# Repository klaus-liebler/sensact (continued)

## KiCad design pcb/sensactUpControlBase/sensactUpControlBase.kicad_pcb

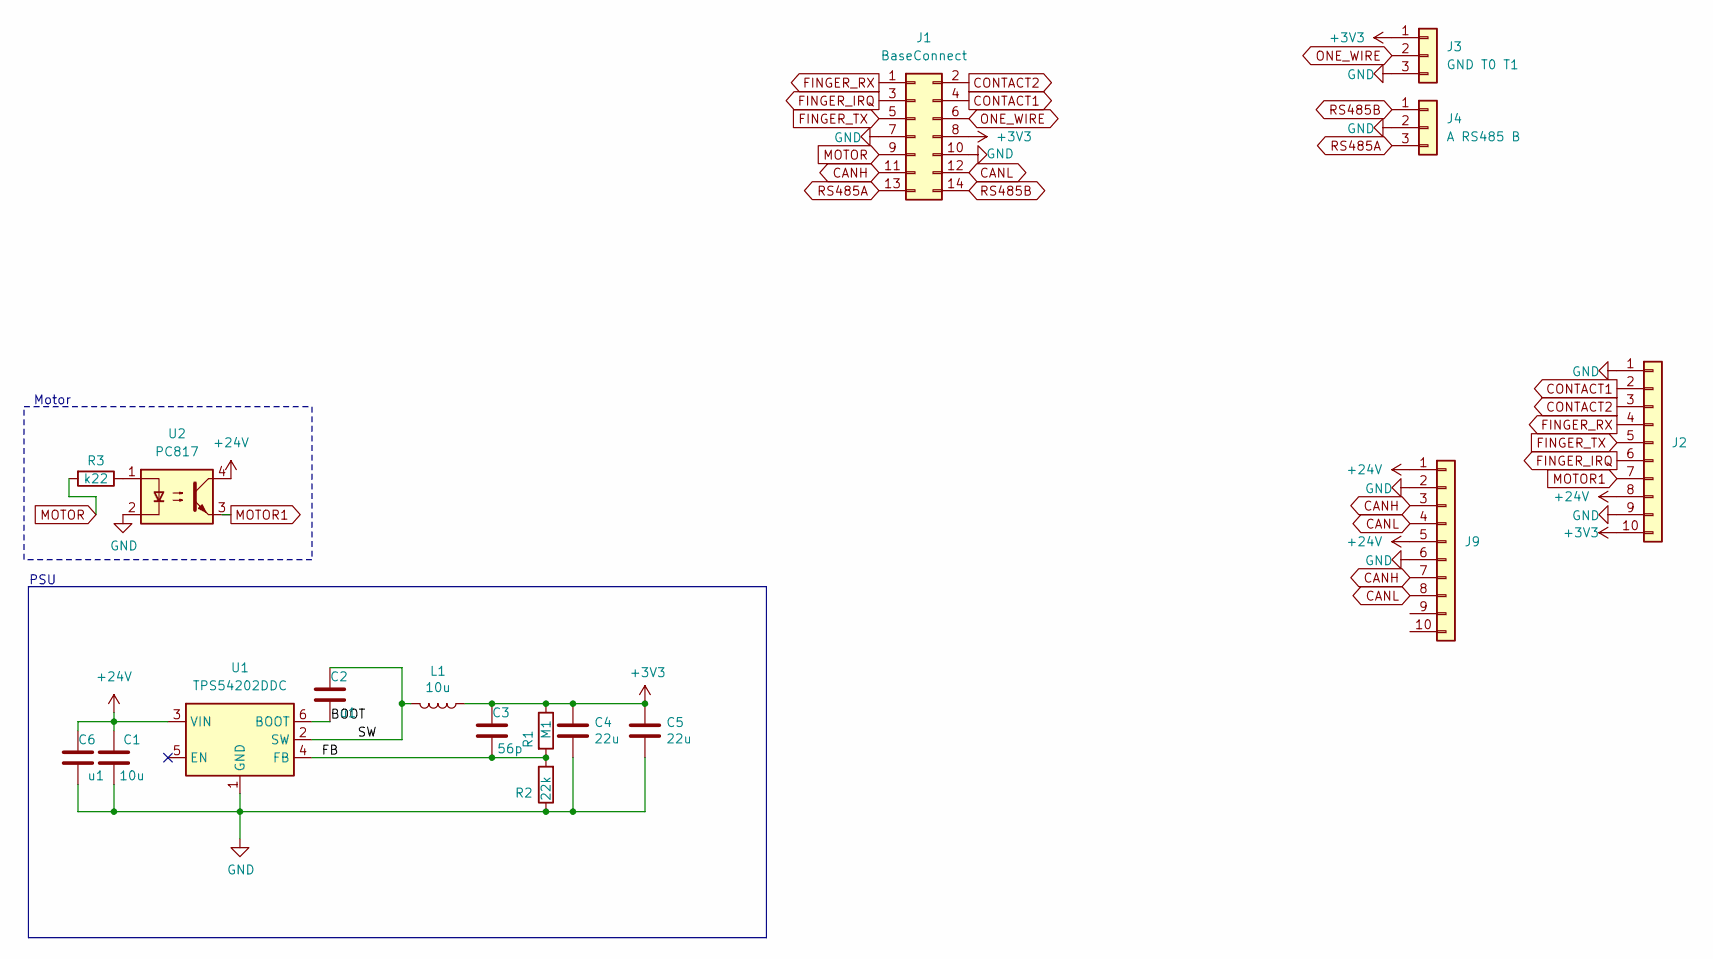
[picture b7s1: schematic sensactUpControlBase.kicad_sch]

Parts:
C1: 10u; C_1206_3216Metric_Pad1.33x1.80mm_HandSolder
C2, C6: u1; C_0805_2012Metric_Pad1.18x1.45mm_HandSolder
C3: 56p; C_0805_2012Metric_Pad1.18x1.45mm_HandSolder
C4, C5: 22u; C_0805_2012Metric_Pad1.18x1.45mm_HandSolder
J1: BaseConnect; PinHeader_2x07_P2.54mm_Vertical
J2, J9: WAGO_250-210
J3: GND T0 T1; WAGO_250_203A
J4: A RS485 B; WAGO_250_203A
L1: 10u; L_0630
R1: M1; R_0805_2012Metric_Pad1.20x1.40mm_HandSolder
R2: 22k; R_0805_2012Metric_Pad1.20x1.40mm_HandSolder
R3: k22; R_0805_2012Metric_Pad1.20x1.40mm_HandSolder
U1: TPS54202DDC; SOT-23-6_Handsoldering
U2: PC817; mdip_4_handsolder

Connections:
+3V3: C3.2, C4.1, C5.1, J1.8, J2.10, J3.1, L1.1, R1.1
+24V: C1.2, C6.2, J2.8, J9.1, J9.5, U1.3 (VIN), U2.4
/BOOT: C2.1, U1.6 (BOOT)
/FB: C3.1, R1.2, R2.2, U1.4 (FB)
/SW: C2.2, L1.2, U1.2 (SW)
CANH: J1.11, J9.3, J9.7
CANL: J1.12, J9.4, J9.8
CONTACT1: J1.4, J2.2
CONTACT2: J1.2, J2.3
FINGER_IRQ: J1.3, J2.6
FINGER_RX: J1.1, J2.4
FINGER_TX: J1.5, J2.5
GND: C1.1, C4.2, C5.2, C6.1, J1.7, J1.10, J2.1, J2.9, J3.3, J4.2, J9.2, J9.6, R2.1, U1.1 (GND), U2.2
MOTOR: J1.9, R3.2
MOTOR1: J2.7, U2.3
unnamed: R3.1, U2.1
ONE_WIRE: J1.6, J3.2
RS485A: J1.13, J4.3
RS485B: J1.14, J4.1

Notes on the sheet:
Motor
PSU

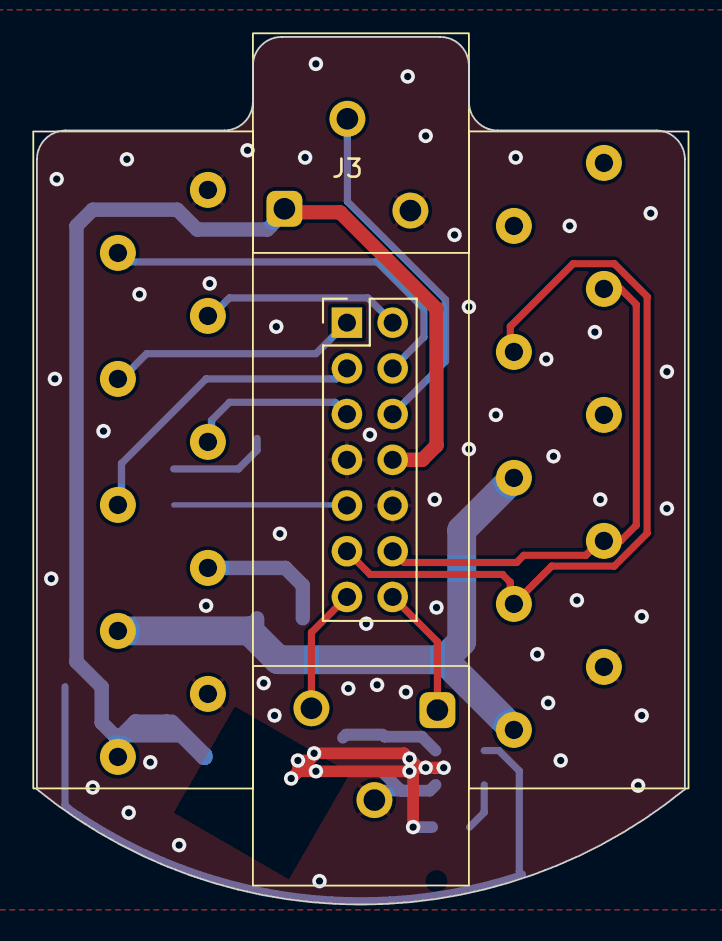
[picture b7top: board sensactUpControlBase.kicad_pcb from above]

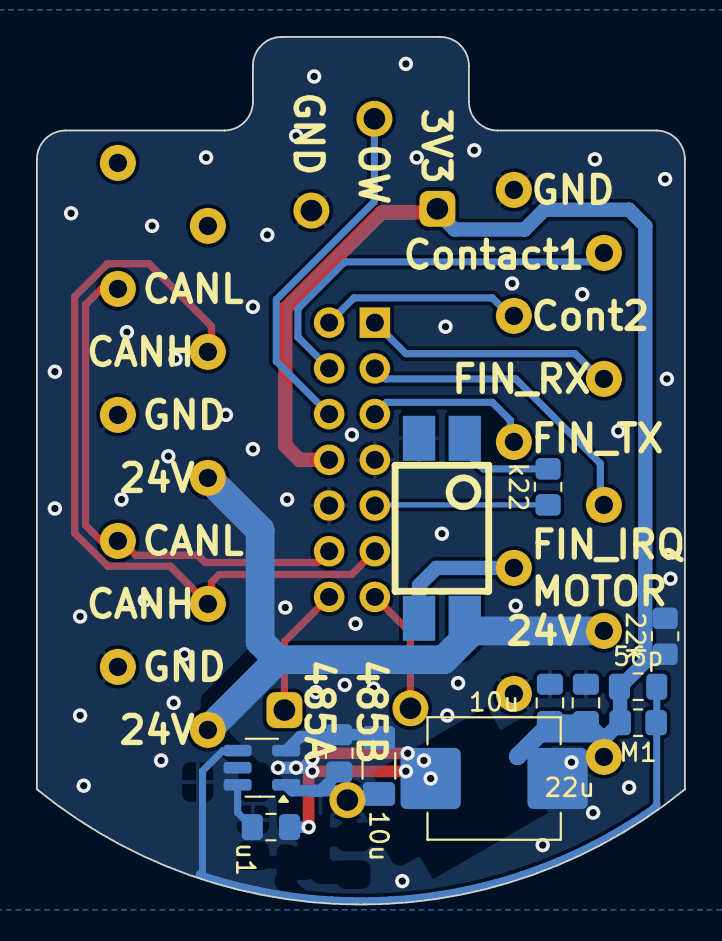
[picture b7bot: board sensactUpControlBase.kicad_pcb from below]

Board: 2 copper layers, 36.0 x 48.2 mm, 17 parts (12 on the bottom side), 19 nets.

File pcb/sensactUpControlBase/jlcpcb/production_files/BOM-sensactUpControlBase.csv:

Comment,Designator,Footprint,LCSC
10u,L1,L_0630,
GND T0 T1,J3,KF250-3.5-3P-A,
BaseConnect,J1,PinHeader_2x07_P2.54mm_Vertical,
~,J9,WAGO_250-210,
A RS485 B,J4,KF250-3.5-3P-A,
~,J2,WAGO_250-210,
22u,C4,C_0805_2012Metric_Pad1.18x1.45mm_HandSolder,
10u,C1,C_1206_3216Metric_Pad1.33x1.80mm_HandSolder,
56p,C3,C_0805_2012Metric_Pad1.18x1.45mm_HandSolder,
u1,C2,C_0805_2012Metric_Pad1.18x1.45mm_HandSolder,
PC817,U2,mdip_4_handsolder,
22u,C5,C_0805_2012Metric_Pad1.18x1.45mm_HandSolder,
22k,R2,R_0805_2012Metric_Pad1.20x1.40mm_HandSolder,
M1,R1,R_0805_2012Metric_Pad1.20x1.40mm_HandSolder,
k22,R3,R_0805_2012Metric_Pad1.20x1.40mm_HandSolder,
TPS54202DDC,U1,SOT-23-6_Handsoldering,

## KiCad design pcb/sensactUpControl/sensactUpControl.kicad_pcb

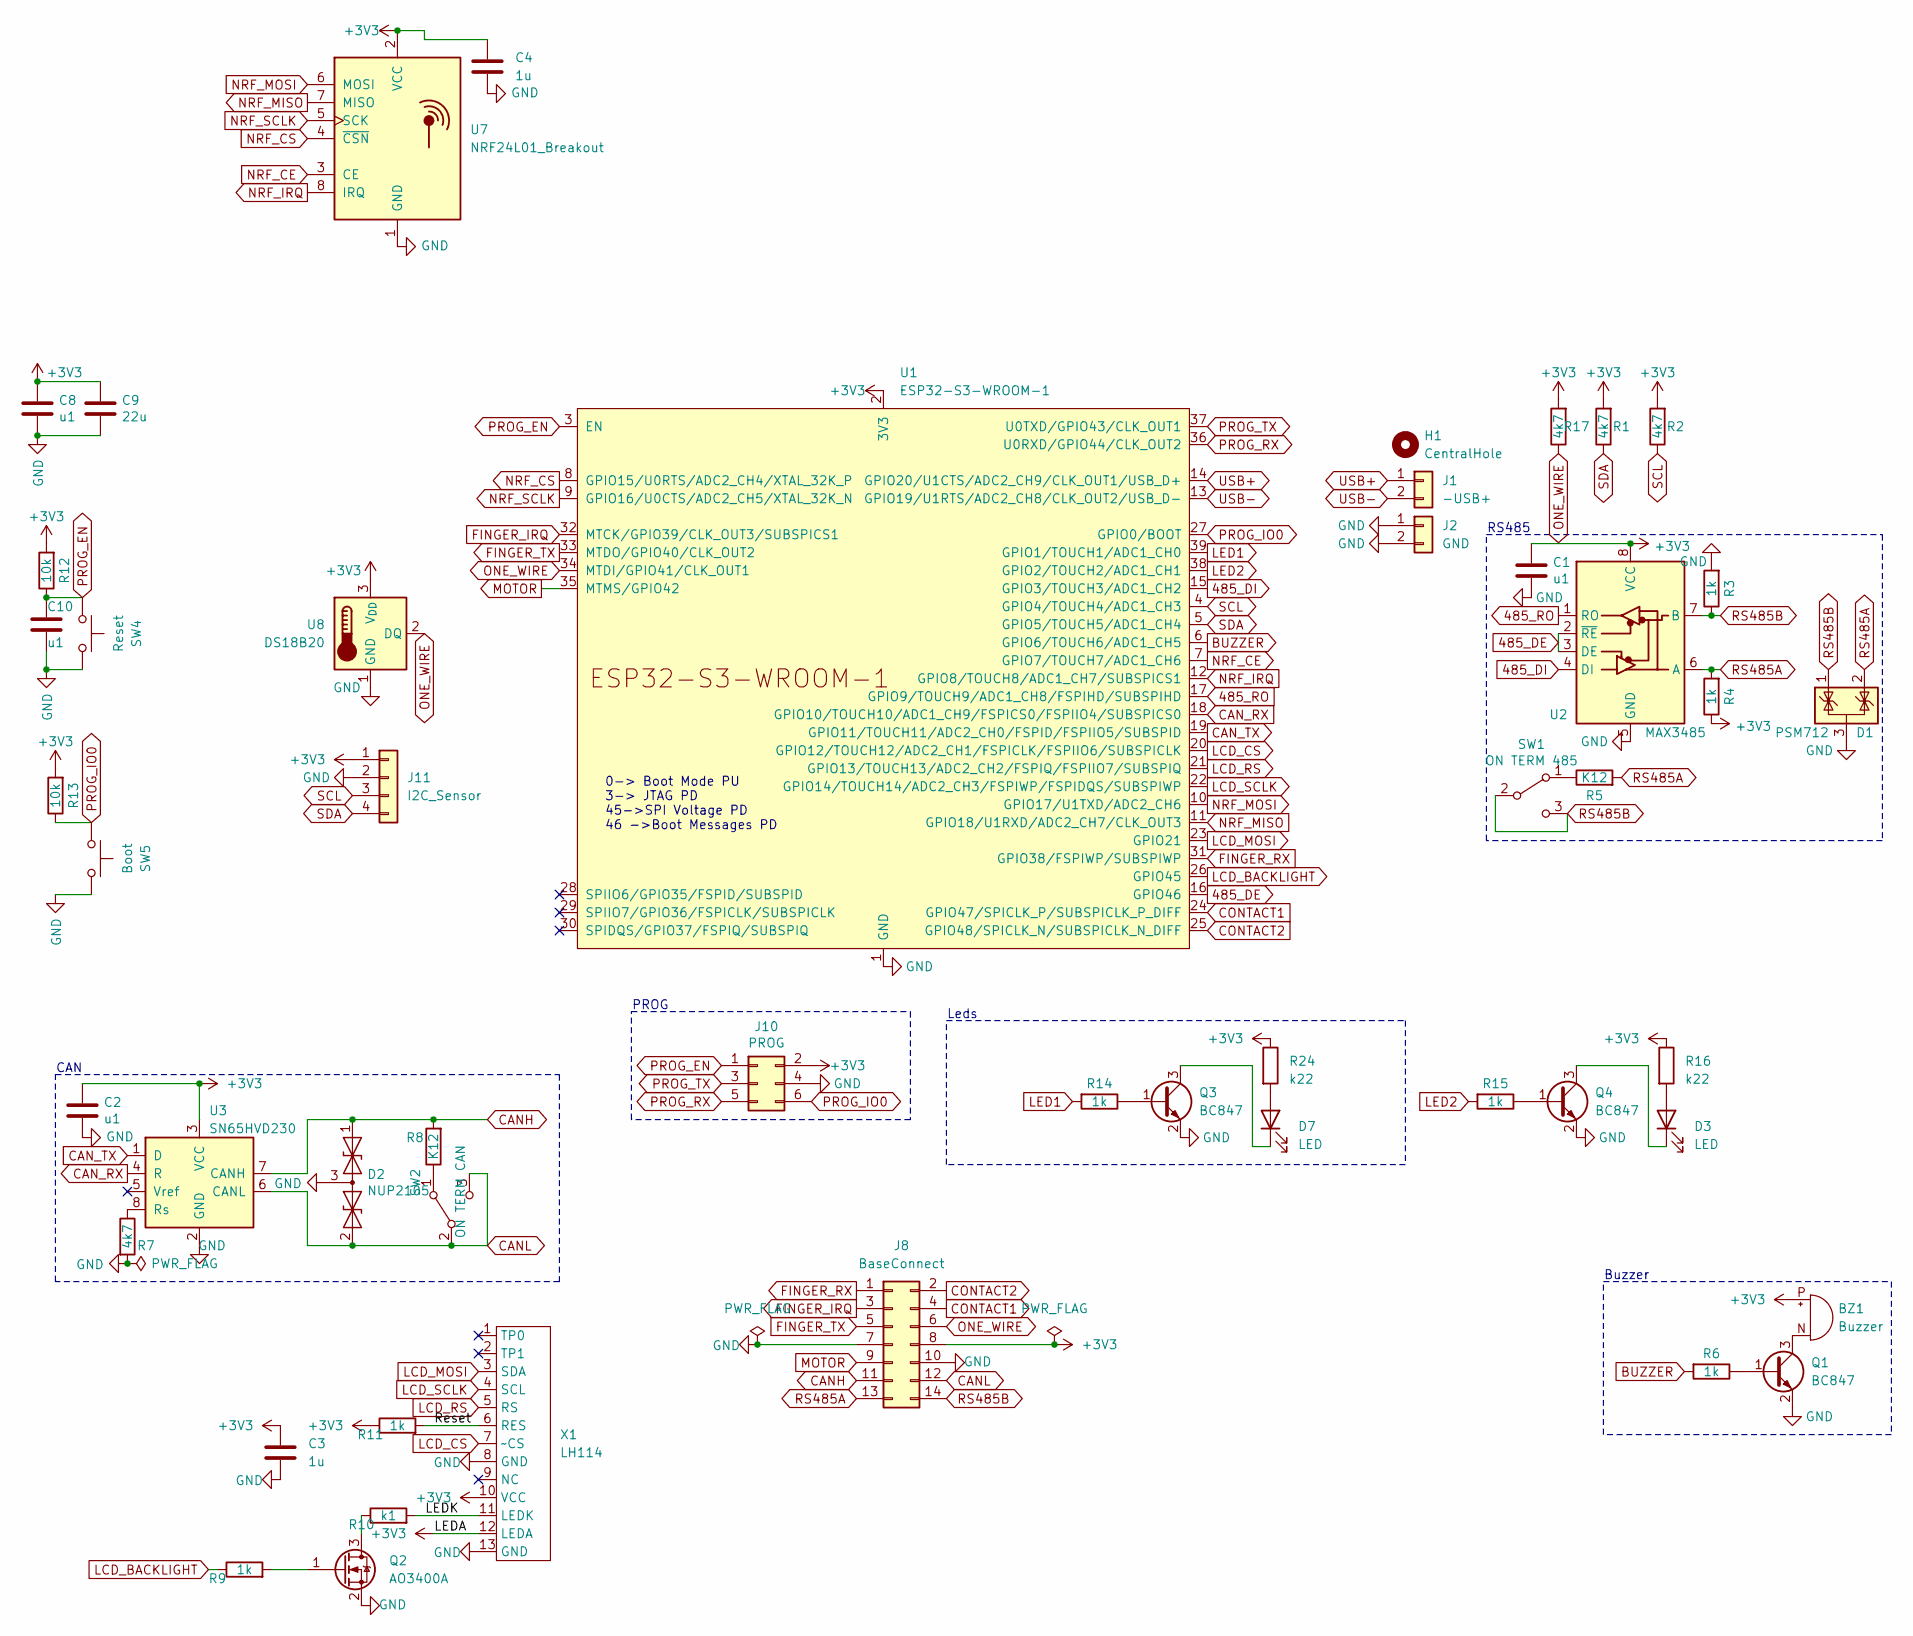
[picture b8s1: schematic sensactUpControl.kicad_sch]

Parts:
BZ1: Buzzer; XDCR_CMT-7525-80-SMT-TR_handsolder
C1, C2, C8, C10: u1; C_0805_2012Metric_Pad1.18x1.45mm_HandSolder
C3, C4: 1u; C_0805_2012Metric_Pad1.18x1.45mm_HandSolder
C9: 22u; C_0805_2012Metric_Pad1.18x1.45mm_HandSolder
D1: PSM712; SOT-23_Handsoldering
D2: NUP2105; SOT-23_Handsoldering
D3, D7: LED; LED_PLCC_2835_Handsoldering
H1: CentralHole; MountingHole_3.2mm_M3
J1: -USB+; PinHeader_1x02_P2.00mm_Vertical
J2: GND; PinHeader_1x02_P2.00mm_Vertical
J8: BaseConnect; PinHeader_2x07_P2.54mm_Vertical
J10: PROG; IDC_2x03_P1.27mm_Vertical
J11: I2C_Sensor; PinHeader_1x04_P2.54mm_Vertical
Q1, Q3, Q4: BC847; SOT-23_Handsoldering
Q2: AO3400A; SOT-23_Handsoldering
R1, R2, R7, R17: 4k7; R_0805_2012Metric_Pad1.20x1.40mm_HandSolder
R3, R4, R6, R9, R11, R14, R15: 1k; R_0805_2012Metric_Pad1.20x1.40mm_HandSolder
R5, R8: K12; R_1206_3216Metric_Pad1.30x1.75mm_HandSolder
R10: k1; R_0805_2012Metric_Pad1.20x1.40mm_HandSolder
R12, R13: 10k; R_0805_2012Metric_Pad1.20x1.40mm_HandSolder
R16, R24: k22; R_1206_3216Metric_Pad1.30x1.75mm_HandSolder
SW1: ON TERM 485; SW_SPDT_PCM12_handsolder
SW2: ON TERM CAN; SW_SPDT_PCM12_handsolder
SW4: Reset; SW_SPST_TL3342_smaller_handsolder
SW5: Boot; SW_SPST_TL3342_smaller_handsolder
U1: ESP32-S3-WROOM-1; ESP32-S3-WROOM-1_handsolder
U2: MAX3485; SOIC-8_3.9x4.9mm_Pitch1.27mm_handsolder
U3: SN65HVD230; SOIC-8_3.9x4.9mm_Pitch1.27mm_handsolder
U7: NRF24L01_Breakout; nRF24L01_Breakout
U8: DS18B20; TO-92_HandSolder
X1: LH114; FP-114 13pol top only

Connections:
485_DE: U1.16 (GPIO46), U2.2 (~RE), U2.3 (DE)
485_DI: U1.15 (GPIO3/TOUCH3/ADC1_CH2), U2.4 (DI)
485_RO: U1.17 (GPIO9/TOUCH9/ADC1_CH8/FSPIHD/SUBSPIHD), U2.1 (RO)
+3V3: BZ1.P (+), C1.2, C2.1, C3.1, C4.1, C8.1, C9.1, J8.8, J10.2, J11.1, R1.2, R2.2, R4.1, R11.1, R12.2, R13.2, R16.1, R17.2, R24.1, U1.2 (3V3), U2.8 (VCC), U3.3 (VCC), U7.2 (VCC), U8.3 (V_{DD}), X1.10 (VCC), X1.12 (LEDA)
/LEDK: R10.2, X1.11 (LEDK)
/Reset: R11.2, X1.6 (RES)
BUZZER: R6.2, U1.6 (GPIO6/TOUCH6/ADC1_CH5)
CANH: D2.1 (A1), J8.11, R8.2, U3.7 (CANH)
CANL: D2.2 (A2), J8.12, SW2.2 (B), SW2.3 (C), U3.6 (CANL)
CAN_RX: U1.18 (GPIO10/TOUCH10/ADC1_CH9/FSPICS0/FSPIIO4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), U3.4 (R)
CAN_TX: U1.19 (GPIO11/TOUCH11/ADC2_CH0/FSPID/FSPIIO5/S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), U3.1 (D)
CONTACT1: J8.4, U1.24 (GPIO47/SPICLK_P/SUBSPICLK_P_DIFF)
CONTACT2: J8.2, U1.25 (GPIO48/SPICLK_N/SUBSPICLK_N_DIFF)
FINGER_IRQ: J8.3, U1.32 (MTCK/GPIO39/CLK_OUT3/SUBSPICS1)
FINGER_RX: J8.1, U1.31 (GPIO38/FSPIWP/SUBSPIWP)
FINGER_TX: J8.5, U1.33 (MTDO/GPIO40/CLK_OUT2)
GND: C1.1, C2.2, C3.2, C4.2, C8.2, C9.2, C10.2, D1.3 (A), D2.3 (common), J2.1, J2.2, J8.7, J8.10, J10.4, J11.2, Q1.2 (E), Q2.2 (S), Q3.2 (E), Q4.2 (E), R3.2, R7.2, SW4.1, SW5.1, U1.1 (GND), U1.40 (GND), U1.41 (GND), U2.5 (GND), U3.2 (GND), U7.1 (GND), U8.1 (GND), X1.8 (GND), X1.13 (GND)
LCD_BACKLIGHT: R9.1, U1.26 (GPIO45)
LCD_CS: U1.20 (GPIO12/TOUCH12/ADC2_CH1/FSPICLK/FSPIIO6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), X1.7 (~CS)
LCD_MOSI: U1.23 (GPIO21), X1.3 (SDA)
LCD_RS: U1.21 (GPIO13/TOUCH13/ADC2_CH2/FSPIQ/FSPIIO7/S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), X1.5 (RS)
LCD_SCLK: U1.22 (GPIO14/TOUCH14/ADC2_CH3/FSPIWP/FSPIDQS/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), X1.4 (SCL)
LED1: R14.2, U1.39 (GPIO1/TOUCH1/ADC1_CH0)
LED2: R15.2, U1.38 (GPIO2/TOUCH2/ADC1_CH1)
MOTOR: J8.9, U1.35 (MTMS/GPIO42)
NRF_CE: U1.7 (GPIO7/TOUCH7/ADC1_CH6), U7.3 (CE)
NRF_CS: U1.8 (GPIO15/U0RTS/ADC2_CH4/XTAL_32K_P), U7.4 (~CSN)
NRF_IRQ: U1.12 (GPIO8/TOUCH8/ADC1_CH7/SUBSPICS1), U7.8 (IRQ)
NRF_MISO: U1.11 (GPIO18/U1RXD/ADC2_CH7/CLK_OUT3), U7.7 (MISO)
NRF_MOSI: U1.10 (GPIO17/U1TXD/ADC2_CH6), U7.6 (MOSI)
NRF_SCLK: U1.9 (GPIO16/U0CTS/ADC2_CH5/XTAL_32K_N), U7.5 (SCK)
unnamed: BZ1.N (-), Q1.3 (C)
unnamed: D3.2 (A), R16.2
unnamed: D3.1 (K), Q4.3 (C)
unnamed: D7.2 (A), R24.2
unnamed: D7.1 (K), Q3.3 (C)
unnamed: Q1.1 (B), R6.1
unnamed: Q2.3 (D), R10.1
unnamed: Q2.1 (G), R9.2
unnamed: Q3.1 (B), R14.1
unnamed: Q4.1 (B), R15.1
unnamed: R5.1, SW1.1 (A)
unnamed: R8.1, SW2.1 (A)
unnamed: R7.1, U3.8 (Rs)
ONE_WIRE: J8.6, R17.1, U1.34 (MTDI/GPIO41/CLK_OUT1), U8.2 (DQ)
PROG_EN: C10.1, J10.1, R12.1, SW4.2, U1.3 (EN)
PROG_IO0: J10.6, R13.1, SW5.2, U1.27 (GPIO0/BOOT)
PROG_RX: J10.5, U1.36 (U0RXD/GPIO44/CLK_OUT2)
PROG_TX: J10.3, U1.37 (U0TXD/GPIO43/CLK_OUT1)
RS485A: D1.2 (K), J8.13, R4.2, R5.2, U2.6 (A)
RS485B: D1.1 (K), J8.14, R3.1, SW1.2 (B), SW1.3 (C), U2.7 (B)
SCL: J11.3, R2.1, U1.4 (GPIO4/TOUCH4/ADC1_CH3)
SDA: J11.4, R1.1, U1.5 (GPIO5/TOUCH5/ADC1_CH4)
USB+: J1.1, U1.14 (GPIO20/U1CTS/ADC2_CH9/CLK_OUT1/USB_D+)
USB-: J1.2, U1.13 (GPIO19/U1RTS/ADC2_CH8/CLK_OUT2/USB_D-)

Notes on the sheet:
Leds
Buzzer
CAN
0-> Boot Mode PU 3-> JTAG PD 45->SPI Voltage PD 46 ->Boot Messages PD
RS485
PROG

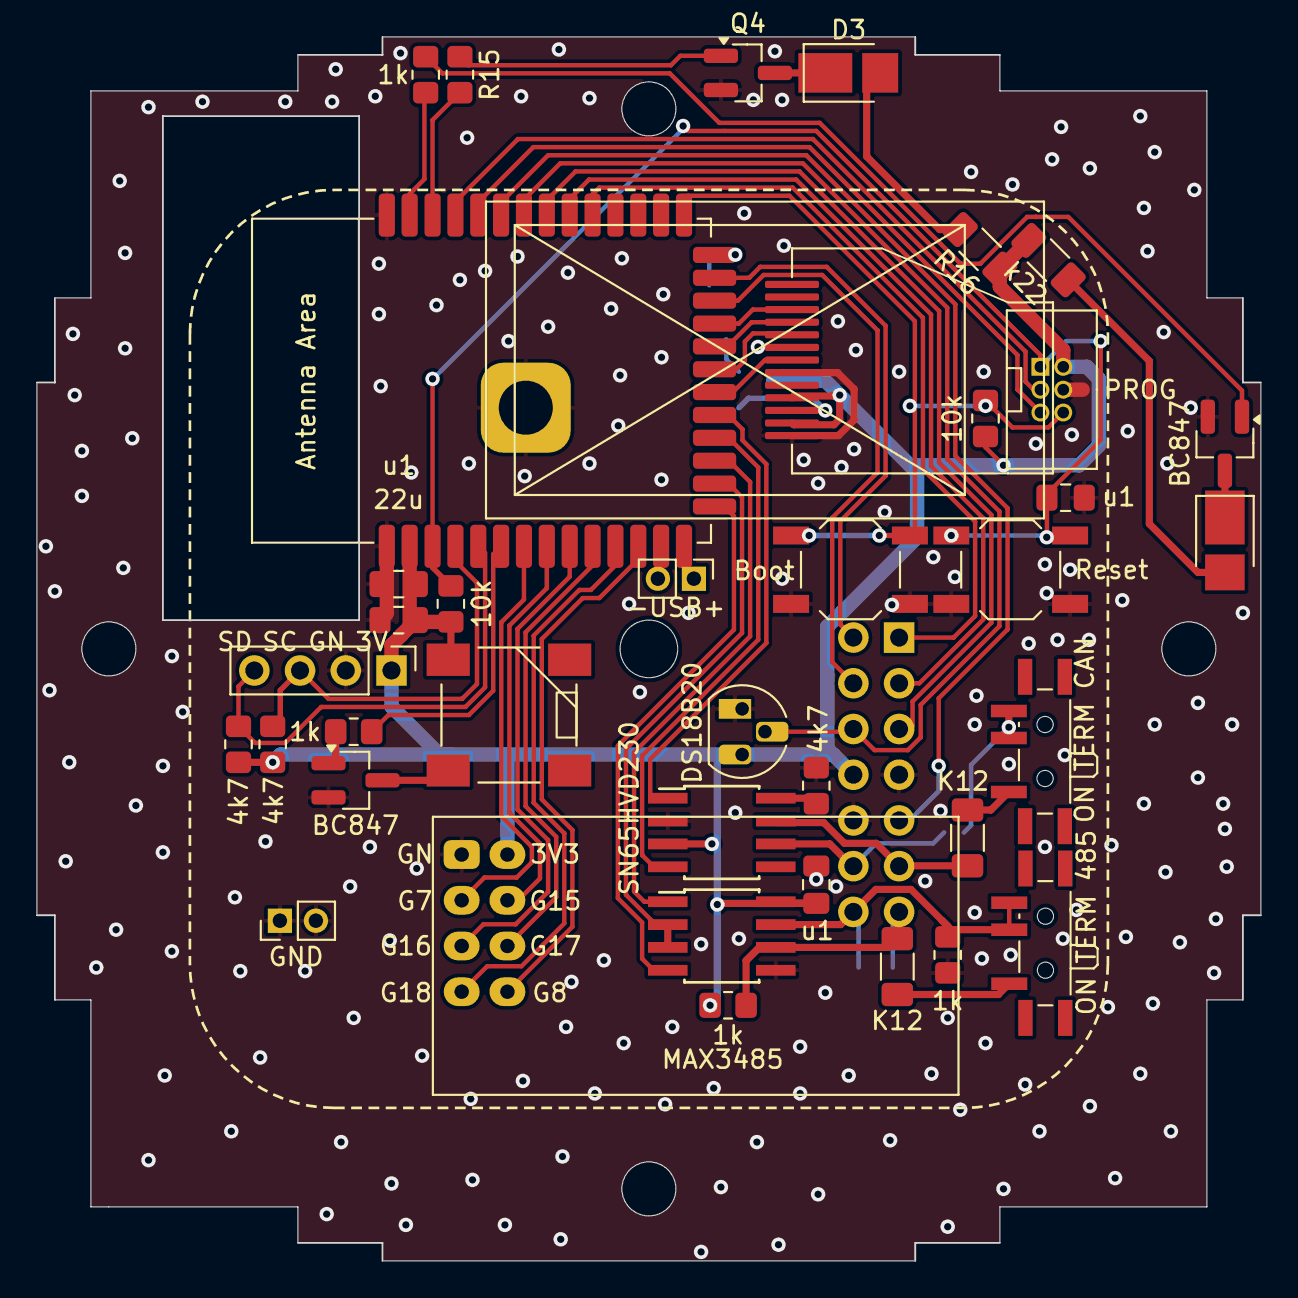
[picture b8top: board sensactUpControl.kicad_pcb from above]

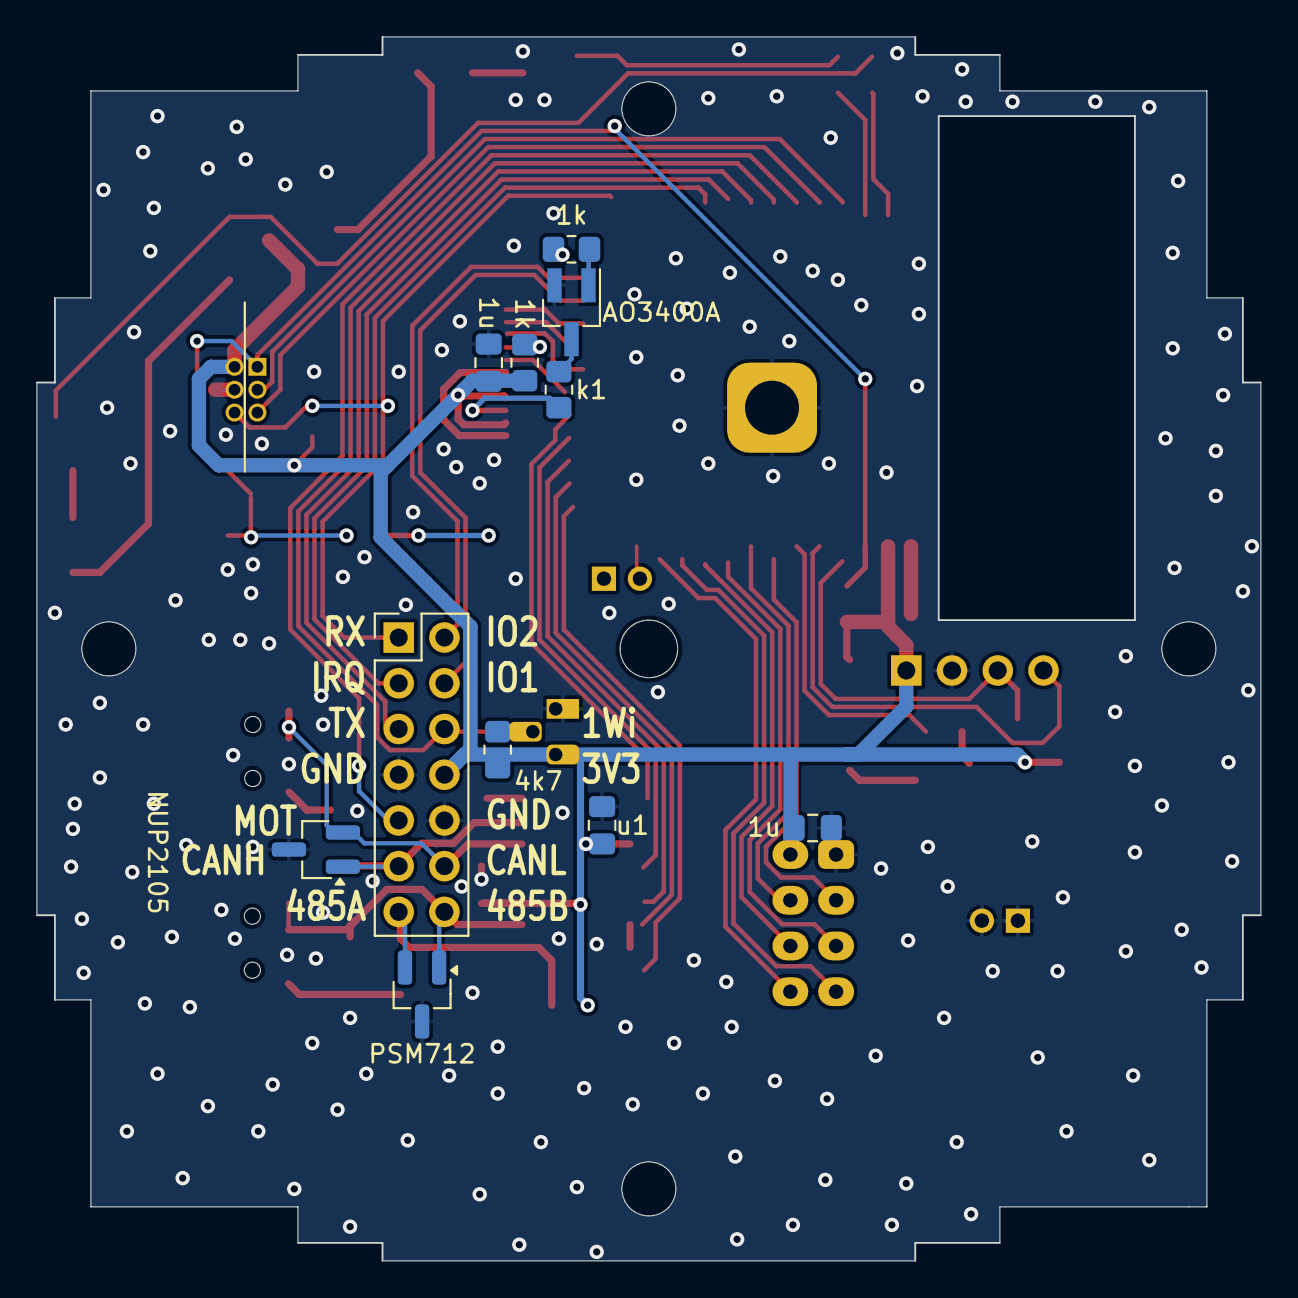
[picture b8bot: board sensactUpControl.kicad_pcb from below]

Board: 2 copper layers, 68.0 x 68.0 mm, 50 parts (11 on the bottom side), 55 nets.

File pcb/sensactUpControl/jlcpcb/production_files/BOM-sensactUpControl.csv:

Comment,Designator,Footprint,LCSC
1k,R3,R_0805_2012Metric_Pad1.20x1.40mm_HandSolder,
MAX3485,U2,SOIC-8_3.9x4.9mm_Pitch1.27mm_handsolder,
4k7,R1,R_0805_2012Metric_Pad1.20x1.40mm_HandSolder,
I2C_Sensor,J11,PinHeader_1x04_P2.54mm_Vertical,
K12,R8,R_1206_3216Metric_Pad1.30x1.75mm_HandSolder,
K12,R5,R_1206_3216Metric_Pad1.30x1.75mm_HandSolder,
22u,C9,C_0805_2012Metric_Pad1.18x1.45mm_HandSolder,
Buzzer,BZ1,XDCR_CMT-7525-80-SMT-TR_handsolder,
BC847,Q1,SOT-23_Handsoldering,
1k,R14,R_0805_2012Metric_Pad1.20x1.40mm_HandSolder,
NRF24L01_Breakout,U7,nRF24L01_Breakout,
10k,R12,R_0805_2012Metric_Pad1.20x1.40mm_HandSolder,
ON TERM CAN,SW2,SW_SPDT_PCM12_handsolder,
4k7,R7,R_0805_2012Metric_Pad1.20x1.40mm_HandSolder,
Boot,SW5,SW_SPST_TL3342_smaller_handsolder,
u1,C1,C_0805_2012Metric_Pad1.18x1.45mm_HandSolder,
GND,J2,PinHeader_1x02_P2.00mm_Vertical,
4k7,R2,R_0805_2012Metric_Pad1.20x1.40mm_HandSolder,
LED,D7,LED_PLCC_2835_Handsoldering,
ESP32-S3-WROOM-1,U1,ESP32-WROOM-32_HANDSOLDER,
CentralHole,H1,MountingHole_3.2mm_M3,
-USB+,J1,PinHeader_1x02_P2.00mm_Vertical,
DS18B20,U8,TO-92_HandSolder,
1k,R4,R_0805_2012Metric_Pad1.20x1.40mm_HandSolder,
LH114,X1,FP-114 13pol top only,
PROG,J10,IDC_2x03_P1.27mm_Vertical,
k22,R24,R_1206_3216Metric_Pad1.30x1.75mm_HandSolder,
Reset,SW4,SW_SPST_TL3342_smaller_handsolder,
u1,C10,C_0805_2012Metric_Pad1.18x1.45mm_HandSolder,
SN65HVD230,U3,SOIC-8_3.9x4.9mm_Pitch1.27mm_handsolder,
1k,R6,R_0805_2012Metric_Pad1.20x1.40mm_HandSolder,
10k,R13,R_0805_2012Metric_Pad1.20x1.40mm_HandSolder,
u1,C8,C_0805_2012Metric_Pad1.18x1.45mm_HandSolder,
ON TERM 485,SW1,SW_SPDT_PCM12_handsolder,
BC847,Q3,SOT-23_Handsoldering,
PSM712,D1,SOT-23_Handsoldering,
1k,R11,R_0805_2012Metric_Pad1.20x1.40mm_HandSolder,
4k7,R17,R_0805_2012Metric_Pad1.20x1.40mm_HandSolder,
1k,R9,R_0805_2012Metric_Pad1.20x1.40mm_HandSolder,
u1,C2,C_0805_2012Metric_Pad1.18x1.45mm_HandSolder,
BaseConnect,J8,PinHeader_2x07_P2.54mm_Vertical,
NUP2105,D2,SOT-23_Handsoldering,
k1,R10,R_0805_2012Metric_Pad1.20x1.40mm_HandSolder,
1u,C3,C_0805_2012Metric_Pad1.18x1.45mm_HandSolder,
1u,C4,C_0805_2012Metric_Pad1.18x1.45mm_HandSolder,

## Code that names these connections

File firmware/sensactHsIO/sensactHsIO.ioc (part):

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Mcu.Name=STM32F072R(8-B)Tx
Mcu.Package=LQFP64
Mcu.UserName=STM32F072RBTx
PA10.Mode=Asynchronous
PA10.Signal=USART1_RX
PA11.Mode=Device
PA11.Signal=USB_DM
PA12.Mode=Device
PA12.Signal=USB_DP
PA13.Mode=Serial_Wire
PA13.Signal=SYS_SWDIO
PA14.Mode=Serial_Wire
PA14.Signal=SYS_SWCLK
PA15.GPIOParameters=GPIO_Label
PA15.GPIO_Label=INT2
PA15.Signal=GPIO_Input
PA2.Mode=Asynchronous
PA2.Signal=USART2_TX
PA3.Mode=Asynchronous
PA3.Signal=USART2_RX
PA6.GPIOParameters=GPIO_Label
PA6.GPIO_Label=I06
PA6.Signal=GPIO_Input
PA7.GPIOParameters=GPIO_Label
PA7.GPIO_Label=I07
PA7.Signal=GPIO_Input
PA8.GPIOParameters=GPIO_Label
PA8.GPIO_Label=VBUS
PA8.Signal=GPIO_Input
PA9.Mode=Asynchronous
PA9.Signal=USART1_TX
PB0.GPIOParameters=GPIO_Label
PB0.GPIO_Label=I02
PB0.Signal=GPIO_Input
PB1.GPIOParameters=GPIO_Label
PB1.GPIO_Label=I03
PB1.Signal=GPIO_Input
PB10.GPIOParameters=GPIO_Label
PB10.GPIO_Label=SCL
PB10.Mode=I2C
PB10.Signal=I2C2_SCL
PB11.GPIOParameters=GPIO_Label
PB11.GPIO_Label=SDA
PB11.Mode=I2C
PB11.Signal=I2C2_SDA
PB12.GPIOParameters=GPIO_Label
PB12.GPIO_Label=SPIB_CS
PB12.Signal=GPIO_Output
PB13.GPIOParameters=GPIO_Label
PB13.GPIO_Label=SPIB_CLK
PB13.Mode=Full_Duplex_Master
PB13.Signal=SPI2_SCK
PB14.GPIOParameters=GPIO_Label
PB14.GPIO_Label=SPIB_MISO
PB14.Mode=Full_Duplex_Master
PB14.Signal=SPI2_MISO
PB15.GPIOParameters=GPIO_Label
PB15.GPIO_Label=SPIB_MOSI
PB15.Mode=Full_Duplex_Master
PB15.Signal=SPI2_MOSI
PB2.GPIOParameters=GPIO_Label
PB2.GPIO_Label=ROTS
PB2.Signal=GPIO_Input
PB3.GPIOParameters=GPIO_Label
PB3.GPIO_Label=LCD_CLK
PB3.Mode=TX_Only_Simplex_Unidirect_Master
PB3.Signal=SPI1_SCK
PB4.GPIOParameters=GPIO_Label
PB4.GPIO_Label=I12
PB4.Signal=GPIO_Input
PB5.GPIOParameters=GPIO_Label
PB5.GPIO_Label=LCD_MOSI
PB5.Mode=TX_Only_Simplex_Unidirect_Master
PB5.Signal=SPI1_MOSI
PB6.GPIOParameters=GPIO_Label
PB6.GPIO_Label=LCD_RS
PB6.Signal=GPIO_Output
PB7.GPIOParameters=GPIO_Label
PB7.GPIO_Label=LCD_BL
PB7.Signal=GPIO_Output
PB8.Mode=Master
PB8.Signal=CAN_RX
PB9.Mode=Master
PB9.Signal=CAN_TX
PC0.GPIOParameters=GPIO_Label
PC0.GPIO_Label=I10
PC0.Signal=GPIO_Input
PC1.GPIOParameters=GPIO_Label
PC1.GPIO_Label=I11
PC1.Signal=GPIO_Input
PC12.GPIOParameters=GPIO_Label
PC12.GPIO_Label=LCD_RST
PC12.Signal=GPIO_Output
PC13.GPIOParameters=GPIO_Label
PC13.GPIO_Label=I13
PC13.Signal=GPIO_Input
PC14-OSC32_IN.GPIOParameters=GPIO_Label
PC14-OSC32_IN.GPIO_Label=I14
PC14-OSC32_IN.Signal=GPIO_Input
PC15-OSC32_OUT.GPIOParameters=GPIO_Label
PC15-OSC32_OUT.GPIO_Label=I15
PC15-OSC32_OUT.Signal=GPIO_Input
PC2.GPIOParameters=GPIO_Label
PC2.GPIO_Label=I04
PC2.Signal=GPIO_Input
PC3.GPIOParameters=GPIO_Label
PC3.GPIO_Label=I05
PC3.Signal=GPIO_Input
PC4.GPIOParameters=GPIO_Label
PC4.GPIO_Label=I00
PC4.Signal=GPIO_Input
PC5.GPIOParameters=GPIO_Label
PC5.GPIO_Label=I01
PC5.Signal=GPIO_Input
PC6.GPIOParameters=GPIO_Label
PC6.GPIO_Label=ROTB
PC6.Signal=S_TIM3_CH1
PC7.GPIOParameters=GPIO_Label
PC7.GPIO_Label=ROTA
PC7.Signal=S_TIM3_CH2
PC8.GPIOParameters=GPIO_Label
PC8.GPIO_Label=INT0
PC8.Signal=GPIO_Input
PC9.GPIOParameters=GPIO_Label
PC9.GPIO_Label=INT1
PC9.Signal=GPIO_Input
PD2.GPIOParameters=GPIO_Label
PD2.GPIO_Label=LCD_CS
PD2.Signal=GPIO_Output
PF0-OSC_IN.GPIOParameters=GPIO_Label
PF0-OSC_IN.GPIO_Label=I08
PF0-OSC_IN.Signal=GPIO_Input
PF1-OSC_OUT.GPIOParameters=GPIO_Label
PF1-OSC_OUT.GPIO_Label=I09
PF1-OSC_OUT.Signal=GPIO_Input
RCC.SYSCLKFreq_VALUE=48000000
RCC.SYSCLKSource=RCC_SYSCLKSOURCE_HSI48
board=custom

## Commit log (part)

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2016-07-24 Fixed doubled App in Sattlerstraße
2016-07-25 sensactSE Changes
2016-07-29 I2C-Search at start, PWM-App gets new Command
2016-07-29 TestGUI
2016-07-29 Fix Build
2016-08-05 Fixed Binary command parser
2016-08-05 OneWire slave test implementation
2016-08-05 PWM - SetVerticalTarget Handler
2016-08-06 Binary commands for the shell; 1Wire with alarm search
2016-08-06 Added OneWire-Commands in the shell, fixed USART3_IRQHandler
2016-08-07 Git SHA key gets compiled in Source, Code for parsing and sending commands is generated
2016-08-13 Fixes/Formatting
2016-08-13 Nodes get their own ID
2016-08-13 Changes in Testmodels
2016-08-13 Updated Sattlerstraße
2016-08-14 Check for double used pins + correction in Sattlerstraße16
2016-08-16 Bugfixes, BLIND-Demo, Formatting, Update to CubeF1 1.4
2016-08-17 Fixed Typo
2016-08-17 Added Terminal view
2016-08-18 Added GeneratedConstants
2016-08-23 Removed PreBuildEvent
2016-08-27 Bugfixes & improved logging
2016-08-27 "Doubleclick" event for pushbutton. systemClock and steadyClock, minor enhancements
2016-08-27 Update Project files
2016-09-06 New PCBs (Extensions)
2016-09-06 Minor Fixes in Configware
2016-09-06 Bugfixes in Firmware
2016-09-06 PCB fixes
2016-09-24 sensactPWMExt as ordered
2016-09-24 Blind-Application: Direction Relay is configurable
2016-09-24 Fixed merge conflicts
2016-09-26 SensactInpExt
2016-09-27 Another update for Model
2016-09-28 Unspecified
2016-09-30 Improved logging and Timeout
2016-10-01 Fix Build & fail safe i2c
2016-10-02 Added Error COunter
2016-10-02 new version of sensactHs
2016-10-02 Using ErrorCounters
2016-10-02 Bugfix in Model
2016-10-09 Änderungen Baustelle
2016-10-09 sensactHS intermediate backup
2016-10-09 Implemented i2c-Reset for STM32F1
2016-10-12 Reset pca9685 properly
2016-10-12 sensactHS Backup
2016-10-15 sensact1.0 first ERC ok
2016-10-17 Bugfixes @ Baustelle
2016-10-18 Finalizing sensactHS 1.0
2016-10-19 Added VBAT-Standby
2016-10-21 Smaller StepDown Regulator
2016-10-21 Infoline
2016-10-21 PCB Update
2016-10-21 Fixed AppId->Index-Mapping
2016-10-21 Merged PCB (manually)
2016-10-22 Standby for soundapp
2016-10-22 Fixes from Baustellle
2016-10-22 Improved PSU
2016-10-22 Digital Filter for rotary encoder, Bugfix in cSound
2016-10-26 Permanent CAN Process
2016-11-20 Various Changes
2016-11-28 Added EventTypes
2016-11-28 Replaced defines with const
2016-11-28 Better MictoUsbVertical-Connector
2016-12-17 Redesign sensactUü
2016-12-17 Redesign sensactPwmExt
2016-12-17 Redesign sensactInpExt
2016-12-17 New Footprints and Parts
2016-12-17 Some Improvement in sensactHs
2016-12-17 New Function SetOutputFull
2016-12-17 Configuration App knows about ForwarderApplication + minor fixes
2016-12-17 New Datasheet
2016-12-17 Minor refactoring
2016-12-17 ForwarderApplication
2017-01-23 Finalize Extension Modules PCB order
2017-01-23 sensactUP modification
2017-01-30 sensactHsmini; initial Version
2017-02-22 Fix build, updated libs
2017-02-22 updated pcb
2017-03-10 Huge Refactoring; still untested
2017-03-28 PCB Order for sensactUP
2017-03-28 Updated Model
2017-03-28 Updates in BoardSupport
2017-05-15 Various updates
2017-05-15 Added documentation for F0 and F4
2017-06-17 Fixes in Sattlerstraße16 config
2017-06-17 Updated ideas
2017-06-17 various updates/fixes in the driver modules
2017-06-17 New module for W5100 ethernet chip
2017-06-17 Fix project setup
2017-06-17 Minor improvement in PCB
2017-06-28 Added LAN8720-doc
2017-06-28 added ESP32-pinout
2017-06-28 Deleted unnecessary cubeMX project
2017-06-28 Removed comments
2017-06-28 Updated to new HAL-Library
2017-06-28 Added UDP test software
2017-06-28 Pulled out constructor from h file
2017-07-11 Huge Refactoring
    Added Ethernet/MQTT/HTTP
    Removed Names/applicationType in all application objects as this information is stored centralle
2017-07-11 Renamed ethernettestF4 to sensactHS100
2017-07-11 SensactUP gets LIN-Port and alternative 5V Power Supply
2017-07-11 Two new PCB symbol (necessary for previous commit)
2017-07-11 Updated error tracking file
2017-07-11 Better mounting Holes for sensactSE
2017-07-12 More Voltage pins
2017-07-24 sensactUP - going further
2017-07-27 PCB Order @ smart-prototyping 2017-07-26
2017-07-27 Added MQTT % CSS811
2017-07-30 Firmware as flashed to L3_HS on 2017-07-30
2017-08-02 Important fix to "Firmware as flashed to L3_HS on 2017-07-30"
2017-08-02 sensactLEDDriver on 5x5cm PCB
2017-08-14 LedDriver refinement
2017-09-07 Every application knows its apptype
2017-10-02 sensactUP04
    Rename eAppResult --> eAppCallResult
    Minor fixes for sensactUP04
2017-10-04 Heartbeat-Buffer with 3 elements
2017-10-04 Use AutoOnInterval
2017-10-04 Updated Sattlerstraße16 according to latest Klemmenplan.xlsx
2017-11-11 Release 11.11.2017 to all UP-Devices
2018-01-05 Various changes as flashed to NODE_SNSCT_L0_TECH_HS_1
2018-03-23 sensactPI
    sensactPI
2018-04-05 RaspiHat
2018-04-20 rpihat release candidate
2018-04-20 firmware for sensactpihat
2018-04-20 related to previous commit
2019-07-12 Updae VisualStudio
2019-07-12 WHS lIb
    WHS lIb
2019-08-17 Update Sattlerstraße16.c mit neuen Schützbezeichnungen
2019-08-24 Deleted old kicad libraries
2019-08-25 Update cBsp for new CAN-HAL-functions
2019-08-25 Hardware docs
2019-09-16 sensactHSExt and sensactAudioExt
2019-09-16 Better "includes" for all files
2019-09-16 Configware creates Source with correct includes
2019-10-07 sensactHsIO Firmware first commit
2019-10-07 sensactUSBBridge first commit
2019-10-07 Deleted old atollic project
2019-10-29 Bump DotNetZip from 1.10.1 to 1.11.0 in /configware/IAPWriter
    Bumps [DotNetZip](https://github.com/haf/DotNetZip.Semverd) from 1.10.1 to 1.11.0.
    - [Release notes](https://github.com/haf/DotNetZip.Semverd/releases)
    - [Commits](https://github.com/haf/DotNetZip.Semverd/commits)
2019-11-01 Deleted old Projects (Sicherung im 7z-File)
2019-11-01 Sicherung der alten Projektdateien
2019-11-01 KiCad sensactHsIO
2019-11-01 Configware erhält weitere Testapplikation
2019-11-01 Erweiterung Dokumentation
2019-11-01 Sensact Firmware RC1
2019-11-09 sensactHsIO as ordered at PCB Service
2019-11-09 sensactHsIO as ordered at JLCPBC (last minute changes)
2019-12-24 Added bevel to corner of PCB
2020-03-10 sensactHsIO2
2020-04-13 updates in sensactHsIO2
2020-11-15 Initial Layout Top board
2021-01-29 Bump log4net from 2.0.3 to 2.0.10 in /configware/Klli.Sensact.Config
    Bumps [log4net](https://github.com/apache/logging-log4net) from 2.0.3 to 2.0.10.
    - [Release notes](https://github.com/apache/logging-log4net/releases)
    - [Changelog](https://github.com/apache/logging-log4net/blob/master/ReleaseInstructions.txt)
    - [Commits](https://github.com/apache/logging-log4net/commits/rel/2.0.10)
2021-02-15 PIO-based firmware (untested)
2021-02-15 sensactHsNano & sensactHsIO3
2021-03-08 Tried various things to find out more about strange debug behaviour
2021-03-13 sensactOutdoor - pretty schematic & 3D rendering
2021-03-14 Added RX470B 433MHz Module
2021-03-15 added fuse , optimized routing
2021-03-15 Unsafed Changes (belongs to the previous checkin)
2021-03-17 Mains Detection
2021-03-18 sensactOutdoor PCB as ordered at JLCPCB
2021-04-08 variousChanges on sensactHSIO3+4 and sensactOutdoor
2021-04-20 firmware sensactOutdoor ported to flatbuffers
2021-04-20 Improvements in pcb design of sensactOutdoor and sensactHsIO4
2021-05-11 Bump hosted-git-info from 2.8.8 to 2.8.9 in /firmware_sensactOutdoor
    Bumps [hosted-git-info](https://github.com/npm/hosted-git-info) from 2.8.8 to 2.8.9.
    - [Release notes](https://github.com/npm/hosted-git-info/releases)
    - [Changelog](https://github.com/npm/hosted-git-info/blob/v2.8.9/CHANGELOG.md)
    - [Commits](https://github.com/npm/hosted-git-info/compare/v2.8.8...v2.8.9)
2021-07-02 PCB optimizations
2021-07-06 Various PCB Updates
2021-07-09 Updated sensactHsNano
2021-07-15 Complete reorganisation
2021-09-02 sensactHsNano for Reflow Soldering
2021-10-03 Updated pin mapping
2021-10-06 Minor improvements
2021-11-25 sensactHSnano as ordered @ JLCPCB
2022-01-01 sensactHsNano & sensactHsRelay
2022-04-04 Various changes (does not compile)
2022-04-08 Sicherung
2022-04-08 First successful compilation (completely untested)
2022-06-09 DIn-schiene-seitenwand + sensactHsNano2
2022-06-11 sensactNanoHS2
2022-11-09 sensactUP3 and sensactUPUpdates to KiCad6
2023-01-15 Updated various PCB
2023-02-15 PCBs as ordered at JLCPCB
2023-02-15 Moved components from project to common directory
2023-02-15 Helper for W5500
2023-07-27 Webmanager, ADCButtons, sensactHMI
2024-01-23 sensactDoorControl
2024-01-24 sh connector with jumper
2024-01-24 Improved layout sensactDoorControl
2024-01-28 larger i2c mith io pins
2024-01-30 sensactDoorCtrl PCB as ordered @JLCPCB
2024-01-30 sensactDoorController
2024-02-08 REmoved door controller - outdated!
2024-02-20 DorrControl PCB improved 2.0
2024-03-29 Bump express in /espidf-components/websensact/websensact_testserver
    Bumps [express](https://github.com/expressjs/express) from 4.18.2 to 4.19.2.
    - [Release notes](https://github.com/expressjs/express/releases)
    - [Changelog](https://github.com/expressjs/express/blob/master/History.md)
    - [Commits](https://github.com/expressjs/express/compare/4.18.2...4.19.2)
    ---
    updated-dependencies:
2024-05-13 Minor Changes
2024-05-21 sensactUpControl
2024-05-21 sensactUpControllerBase (WIP)
2024-05-22 sensactUpControl - Layout finished, ready for optimization
2024-05-22 improvements upcontrol
2024-06-03 sensactUPControl changed footprint for ESP32
2024-06-13 Bump braces and gulp in /espidf-components/websensact/websensact_builder
    Bumps [braces](https://github.com/micromatch/braces) to 3.0.3 and updates ancestor dependency [gulp](https://github.com/gulpjs/gulp). These dependencies need to be updated together.
    Updates `braces` from 3.0.2 to 3.0.3
    - [Changelog](https://github.com/micromatch/braces/blob/master/CHANGELOG.md)
    - [Commits](https://github.com/micromatch/braces/compare/3.0.2...3.0.3)
    Updates `gulp` from 4.0.2 to 5.0.0
    - [Release notes](https://github.com/gulpjs/gulp/releases)
2024-06-16 Second LED in sensactUPControl
2024-06-18 Bump ws in /espidf-components/websensact/websensact_testserver
    Bumps [ws](https://github.com/websockets/ws) from 8.14.2 to 8.17.1.
    - [Release notes](https://github.com/websockets/ws/releases)
    - [Commits](https://github.com/websockets/ws/compare/8.14.2...8.17.1)
    ---
    updated-dependencies:
    - dependency-name: ws
2024-08-29 Minor improvement
2024-09-17 sensact refactoring
2024-10-01 Minor refactoring; introducing a context object
2025-02-04 New sensact Outdoor (initial)
2025-02-04 sensactOutdoor WIP
2025-02-04 Version Update
2025-02-08 New sensact web ui
2025-02-12 Updated sensactOutdoor PCB
2025-02-12 Huge refactoring
2025-02-13 Further huge Refactoring
2025-02-17 littlefs, temperatur_sensor_handle, improved journal
2025-02-19 sensactOutdoor PCB wip
2025-02-19 Improved build process
2025-02-21 sensactOutdoor PCD WIP
2025-02-25 New sensactOutdoor for KiCad 9
2025-02-26 sensactOutdoor PCB DRC complete
2025-03-02 sensactOutdoor Release Candidate
2025-03-06 Fixes
2025-03-09 Added Header for MX98357
2025-03-10 Sensact builds again
2025-03-21 sensactOutdoor PCB as ordered @ JLCPCB
2025-03-21 added sensactOutdoor
2025-03-22 Added milight
2025-03-24 moved up configware workspace; Improved milight handling (untested)
2025-03-25 Various fixes
2025-04-04 applicationhost fix
2025-04-06 Various Fixes and logging improvements
2025-04-25 PCB as ordered at JLCPCB
2025-04-25 Configware improvements
2025-04-25 Various fixes for sensact Sattlerstraße
2025-07-02 sensactUp in various versions
2025-07-03 Layout Improvements, added VCML4040
2025-07-07 Updated Footprint ESP32-S3
2025-07-07 DRC OK
2025-07-07 DRC ok (2nd try)
2025-07-10 Improved layout DRC ok
2025-07-10 Further layout improvements
2025-07-16 Various updates in sensactRingEncoder
2025-07-21 Various improvements
2025-07-25 sensactRingEncoder as ordered @ JLCPCB
2025-10-02 sensactUp-as_HS updates
2025-10-02 sensactUP_as_UP forgotten files
2025-10-04 Pin usage according to sensactRingEncoder
2025-10-07 sensactUp_as_Hs
2025-10-07 Fixed comments
2025-10-12 PCB for sensactUp_as_Hs as odered @ JLCPCB
2026-02-19 Deleted old files
2026-02-24 Smaller WebUI, Nodemaster
